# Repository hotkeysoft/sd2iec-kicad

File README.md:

# SD2IEC
Rev A September 2022

### Basic Tests: works, with flaws

This version was built and minimal tests were performed. The footprint for the DIN connectors is wrong. **Don't put in the DIN connectors**. The alternate footprints are fine, I used a cable with a JST connector on one side and a male DIN on the other.

Rev B will have a corrected footprint and maybe more IO connectors (serial, LCD connectors were left out due to routing headache)

You can quote me on this: 
> Triple check your footprints with the real things.
Don't blindly trust a footprint diagram found on AliExpress - me

### Description

Yet another varion of the [SD2IEC](https://www.c64-wiki.com/wiki/SD2IEC) hardware device. From the wiki:

>The SD2IEC is a mass storage device using an SD/MMC card and interfacing with the IEC bus. It is based on the ATmega644 microcontroller from the Atmel AVR microcontroller family. The most prominent use of SD2IEC is replacement of a Commodore-1541 disk drive for a C64. The hardware and the microcontroller sd2iec firmware are available as open source

Compatible with C64, C64DTV, C128 (no burst mode), C16, VIC-20, etc.

### Features of this version:
* Nothing fancy, there are 1001 version out there, it's just mine
* ATmega1284p
	- more headspace
* Reset button
	- only resets the *drive*, not the whole computer nor the other drives
* Full size SD slot
	- *...which happens to be one I had on hand, so **triple check** the layout (holes and pads on the side) to see if it will fit with yours*
* Prev / Next buttons 
	- *Not even sure what they do, need to check the doc*
* Device selection DIP switches (8-11)
* Red / Green LEDs for activity, red flash on error, etc.
* Voltage regulator
	- MIC5504-3.3YM5 LDO regulator
		+ can probably be swapped with another regulator with same footprint
		+ don't put in more than ~6V (5.5 regulator max + diode drop)
		+ ...or less than 4V
	- Powers from the 5V on the datasette connector (optional). 
	- Can solder alternate 5V power source on pads 1 & 2
	- *I'll put in an alternate pin header in RevB...*
* Two DIN connectors with passthrough, so you can daisy chain with another drive or more.
	- **The footprint for the DIN connector is wrong in RevA, don't use it**
* Alternate footprint for the two IEC connectors: Can solder in 2.54mm pin headers instead of the DIN connectors 
	- I put a JST connector in there
	- **Again, don't use the DIN connectors with RevA!**
* The IEC lines are switched with MOSFETS (AO3400A) 
	- *...which are not recommended for new designs and surely out of stock everytwhere (everything is at the moment). There are probably direct replacements*
* Fancy tantalum capacitors which are surely overkill. Not sure what I was thinking. Don't put 'em backwards

Images
============
|Front                                                 | Back                                              |
|------------------------------------------------------|---------------------------------------------------|
|||

### Schematics (pdf)
- [Complete schematics](./img/schema.pdf)

### PCB Images (svg)
- [Top](./img/pcb-front.svg)
- [Bottom](./img/pcb-back.svg)

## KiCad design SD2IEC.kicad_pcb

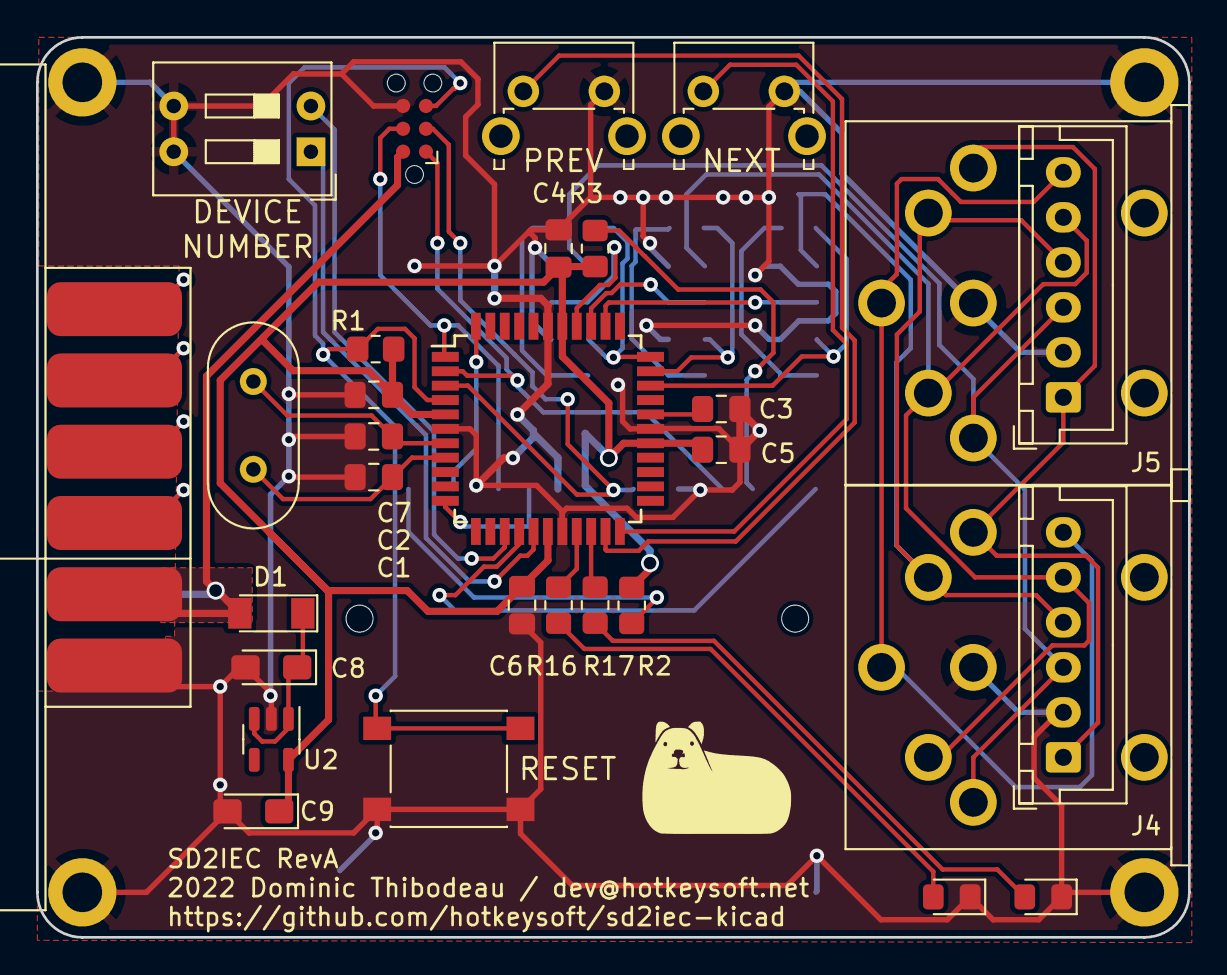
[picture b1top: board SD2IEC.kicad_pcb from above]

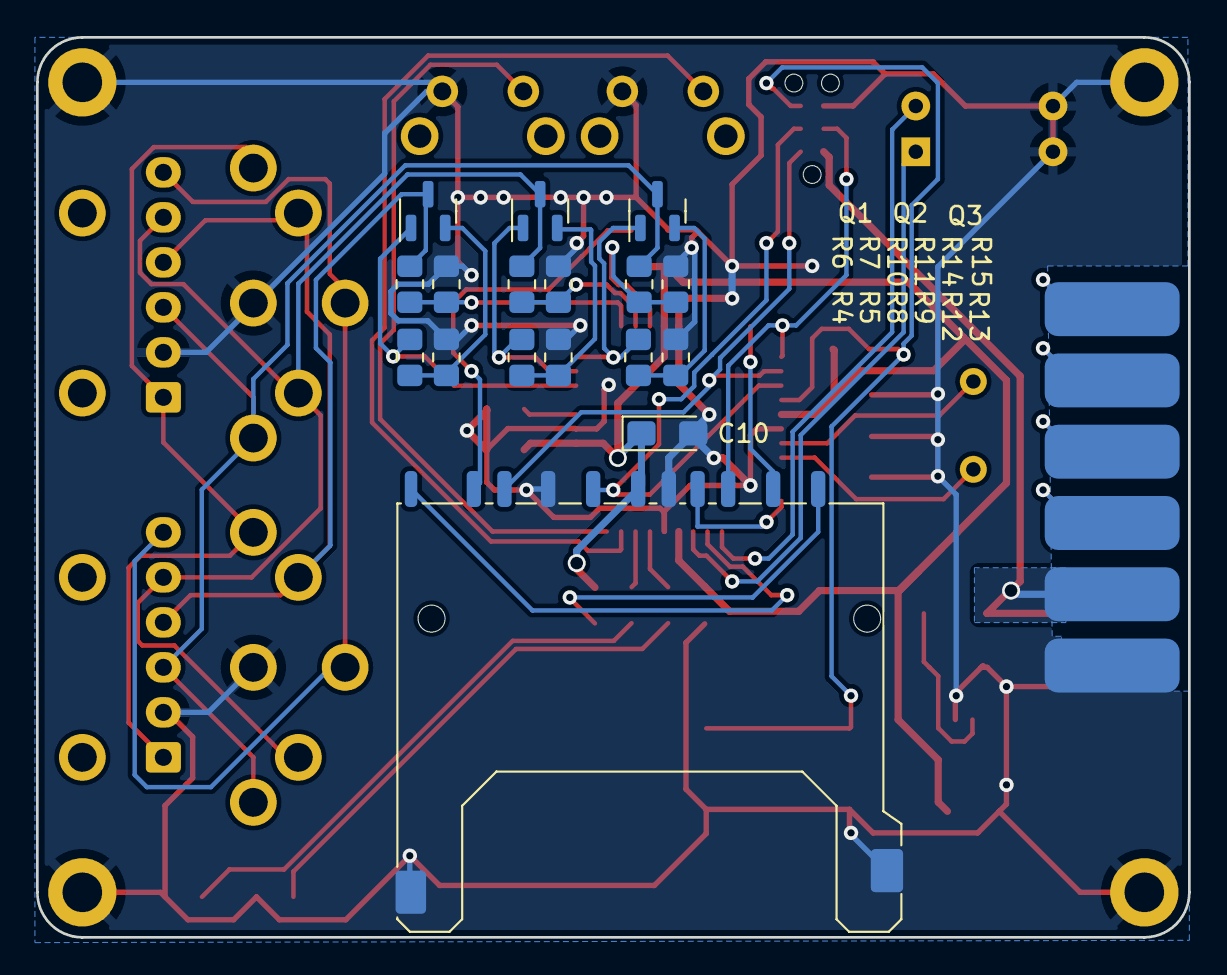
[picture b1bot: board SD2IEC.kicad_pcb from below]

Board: 2 copper layers, 64.0 x 50.0 mm, 51 parts (17 on the bottom side), 38 nets.

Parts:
C1, C2: 56pF; C_0805_2012Metric_Pad1.18x1.45mm_HandSolder
C3, C4, C5, C6, C7: 100nF; C_0805_2012Metric_Pad1.18x1.45mm_HandSolder
C8, C9, C10: 10μF; CP_EIA-3216-10_Kemet-I_Pad1.58x1.35mm_HandSolder
D1: LL4148; D_MiniMELF
D2: RED; LED_0805_2012Metric_Pad1.15x1.40mm_HandSolder
D3: GREEN; LED_0805_2012Metric_Pad1.15x1.40mm_HandSolder
H1, H2, H3, H4: MountingHole_Pad; MountingHole_2.2mm_M2_DIN965_Pad
J1: AVR-ISP-6; Tag-Connect_TC2030-IDC-NL_2x03_P1.27mm_Vertical
J2: 5VDC IN; COMMODORE_CASSETTE_EdgeMount
J3: SD_Card; SD_Kyocera_145638009211859+
J4, J5: IEC (DIN6); DIN6_PCB_RIGHTANGLE
J8: IEC_ALT1; JST_XH_B6B-XH-A_1x06_P2.50mm_Vertical
J9: IEC_ALT2; JST_XH_B6B-XH-A_1x06_P2.50mm_Vertical
Q1, Q2, Q3: AO3400A; SOT-23
R1, R2, R3, R4, R6, R8, R10, R12, R14: 10K; R_0805_2012Metric_Pad1.20x1.40mm_HandSolder
R5, R9, R13: 18R; R_0805_2012Metric_Pad1.20x1.40mm_HandSolder
R7, R11, R15: 22K; R_0805_2012Metric_Pad1.20x1.40mm_HandSolder
R16, R17: 330R; R_0805_2012Metric_Pad1.20x1.40mm_HandSolder
SW1: IEC_SEL; SW_DIP_SPSTx02_Slide_9.78x7.26mm_W7.62mm_P2.54mm
SW2: PREV; SW_Tactile_SPST_Angled_PTS645Vx58-2LFS
SW3: NEXT; SW_Tactile_SPST_Angled_PTS645Vx58-2LFS
SW4: RESET; SW_SPST_PTS645
U1: ATmega1284P-20AU; TQFP-44_10x10mm_P0.8mm
U2: MIC5504-3.3YM5; SOT-23-5
Y1: 8MHz; Crystal_HC49-4H_Vertical

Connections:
+3.3V: C4.2, C5.2, C6.2, C7.2, C9.1, C10.1, J3.4 (VDD), R1.1, R2.2, R3.1, U1.5 (VCC), U1.17 (VCC), U1.27 (AVCC), U1.38 (VCC), U2.5 (VOUT)
+5V: D1.2 (A), J1.2 (VCC), J2.2
/AREF: C3.2, U1.29 (AREF)
/BUSY: R16.2, U1.19 (PC0)
/BUSY_LED: D3.2 (A), R16.1
/DIRTY: R17.2, U1.20 (PC1)
/DIRTY_LED: D2.2 (A), R17.1
/IEC8_9: SW1.2, U1.14 (PD5)
/IEC10_11: SW1.1, U1.16 (PD7)
/IEC_ATN: J4.3, J5.3, J8.3, J9.3, Q3.3 (D), R14.1
/IEC_ATN/READ: R14.2, R15.1, U1.37 (PA0)
/IEC_ATN/WRITE: Q3.1 (G), R12.2, U1.33 (PA4)
/IEC_CLK: J4.4, J5.4, J8.4, J9.4, Q1.3 (D), R6.1
/IEC_CLK/READ: R6.2, R7.1, U1.35 (PA2)
/IEC_CLK/WRITE: Q1.1 (G), R4.2, U1.31 (PA6)
/IEC_DATA: J4.5, J5.5, J8.5, J9.5, Q2.3 (D), R10.1
/IEC_DATA/READ: R10.2, R11.1, U1.36 (PA1)
/IEC_DATA/WRITE: Q2.1 (G), R8.2, U1.32 (PA5)
/MISO: J1.1 (MISO), J3.7 (DAT0), U1.2 (PB6)
/MOSI: J1.4 (MOSI), J3.2 (CMD), U1.1 (PB5)
/NEXT: SW3.1, U1.22 (PC3)
/PREV: SW2.1, U1.21 (PC2)
/SCK: J1.3 (SCK), J3.5 (CLK), U1.3 (PB7)
/~CARD_DETECT: J3.10 (CARD_DETECT), U1.11 (PD2)
/~IEC_RESET: J4.6, J5.6, J8.6, J9.6
/~IEC_SQR: J4.1, J5.1, J8.1, J9.1
/~SD_CS: J3.1 (CD/DAT3), U1.44 (PB4)
/~WRITE_PROTECT: J3.11 (WRITE_PROTECT), U1.15 (PD6)
GND: C1.2, C2.2, C3.1, C4.1, C5.1, C6.1, C7.1, C8.2, C9.2, C10.2, D2.1 (K), D3.1 (K), H1.1, H2.1, H3.1, H4.1, J1.6 (GND), J2.1, J3.3 (VSS), J3.6 (VSS), J3.12 (SHELL1), J3.13 (SHELL2), J4.2, J5.2, J8.2, J9.2, R5.2, R7.2, R9.2, R11.2, R13.2, R15.2, SW1.3, SW1.4, SW2.2, SW3.2, SW4.2, U1.6 (GND), U1.18 (GND), U1.28 (GND), U1.39 (GND), U2.2 (GND)
unnamed: C1.1, U1.8 (XTAL1), Y1.1
unnamed: C2.1, U1.7 (XTAL2), Y1.2
unnamed: C8.1, D1.1 (K), U2.1 (VIN), U2.3 (EN)
unnamed: J1.5 (~RST), R1.2, SW4.1, U1.4 (~RESET)
unnamed: J3.8 (DAT1), R3.2
unnamed: J3.9 (DAT2), R2.1
unnamed: Q1.2 (S), R4.1, R5.1
unnamed: Q2.2 (S), R8.1, R9.1
unnamed: Q3.2 (S), R12.1, R13.1

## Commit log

2021-07-01 Initial import
2021-07-02 Added IEC pin control
2021-07-04 mosfets, switches
2021-07-04 I2C Connector, cleanup
2021-08-13 Added status LEDs, Changed mcu to ATmega1284P (same footprint)
2021-08-14 Move cassette connector offboard
2021-08-16 Board orientation, DIN Connector
2021-08-17 Switched to horizontal compact layout
2022-09-18 KiCad6
2022-09-18 Begin routing
2022-09-19 Cleanup
2022-09-19 Add images
2022-09-19 Add plot
2022-09-27 RevA: Added fab and ibom, updated README
